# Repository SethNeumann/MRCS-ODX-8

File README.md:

# REPO NAME: MRCS-ODX-8
## License: Creative Commons Attribution-NonCommercial-ShareAlike

High Density Expandable cpOD-M motherboard.  Jon Robinson requested a larger motherboard
comparable to Dr. Chubb's ODMB. The requirement is to get as many cpOD-Ms as possible into a 7
x 15 CM board and provide connectors for expansion. Jon also requested keeping the logic 
level outputs away from the block power outputs.  The board will be expandable via an end
connector.  More than two are not recommended as the copper is only good for about 5 Amps.

ODX-8 are backward compatible with current cpOD-Ms, but mechanically will not fit DCC-ODs.
No software changes are needed.

- Board size 2.7" x 5.8" (69x150 mm)

- DCC Bus connections are 5 mm screw terminal blocks or 0.156 connector for expansion

- power, Ground, and Detector output connections are on a 10-position .100 (2.54 mm) screw terminal block.

The ODX-8 provides an economical and convenient mounting for up to eight cpOD-M detectors 

The ODX-8 mounts in DIN-Rail 70mm snap track or with #4 screws

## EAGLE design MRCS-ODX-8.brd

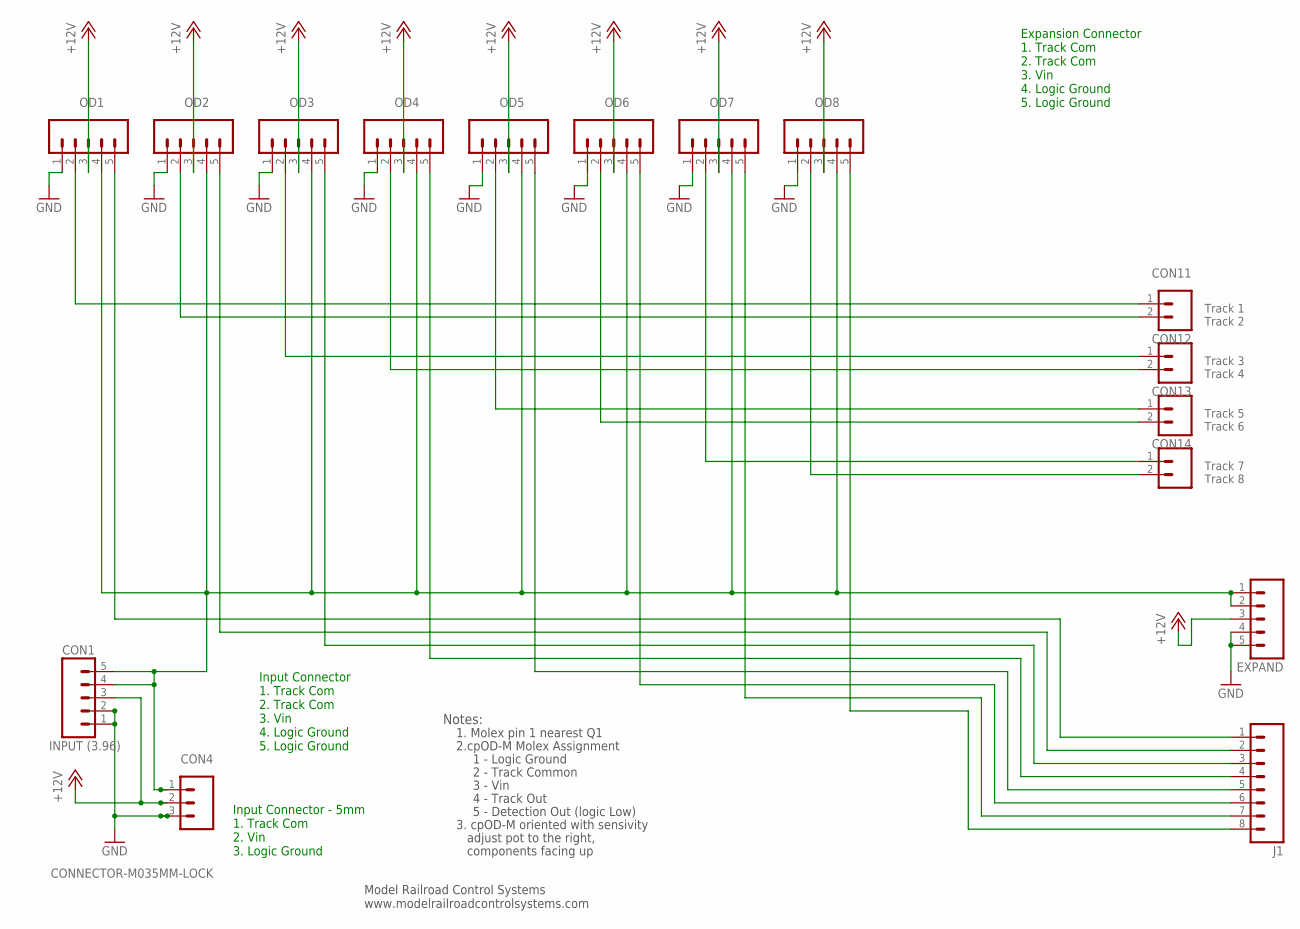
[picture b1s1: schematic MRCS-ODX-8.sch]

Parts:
CON1: INPUT (3.96); KK-156-5
CON4: CONNECTOR-M035MM-LOCK; SCREWTERMINAL-5MM-3
CON11, CON12, CON13, CON14: CONNECTOR-M025MM-LOCK; SCREWTERMINAL-5MM-2
EXPAND: CONNECTOR-M051.56; KK-156-5
J1: CONNECTOR-M08LOCK; 1X08_LOCK
OD1, OD2, OD3, OD4, OD5, OD6, OD7, OD8: CONNECTOR-M051.56; KK-156-5

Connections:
+12V: CON1.3, CON4.2, EXPAND.3, OD1.3, OD2.3, OD3.3, OD4.3, OD5.3, OD6.3, OD7.3, OD8.3
GND: CON1.1, CON1.2, CON4.3, EXPAND.4, EXPAND.5, OD1.1, OD2.1, OD3.1, OD4.1, OD5.1, OD6.1, OD7.1, OD8.1
unnamed: CON14.2 (B), OD8.2
unnamed: CON11.1 (A), OD1.2
unnamed: CON13.2 (B), OD6.2
unnamed: CON13.1 (A), OD5.2
unnamed: J1.2, OD2.5
unnamed: J1.1, OD1.5
unnamed: J1.4, OD4.5
unnamed: J1.5, OD5.5
unnamed: J1.6, OD6.5
unnamed: J1.8, OD8.5
unnamed: J1.7, OD7.5
unnamed: J1.3, OD3.5
unnamed: CON14.1 (A), OD7.2
unnamed: CON12.2 (B), OD4.2
unnamed: CON12.1 (A), OD3.2
unnamed: CON11.2 (B), OD2.2
TRACK_POWER: CON1.4, CON1.5, CON4.1, EXPAND.1, EXPAND.2, OD1.4, OD2.4, OD3.4, OD4.4, OD5.4, OD6.4, OD7.4, OD8.4

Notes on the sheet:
1 - Logic Ground
4 - Track Out
3 - Vin
2 - Track Common
5 - Detection Out (logic Low)
2.cpOD-M Molex Assignment
Notes:
3. cpOD-M oriented with sensivity
adjust pot to the right,
components facing up
Track 1 Track 2
Model Railroad Control Systems www.modelrailroadcontrolsystems.com
1. Molex pin 1 nearest Q1
Input Connector 1. Track Com 2. Track Com 3. Vin 4. Logic Ground 5. Logic Ground
Input Connector - 5mm 1. Track Com 2. Vin 3. Logic Ground
Track 3 Track 4
Track 5 Track 6
Track 7 Track 8
Expansion Connector 1. Track Com 2. Track Com 3. Vin 4. Logic Ground 5. Logic Ground

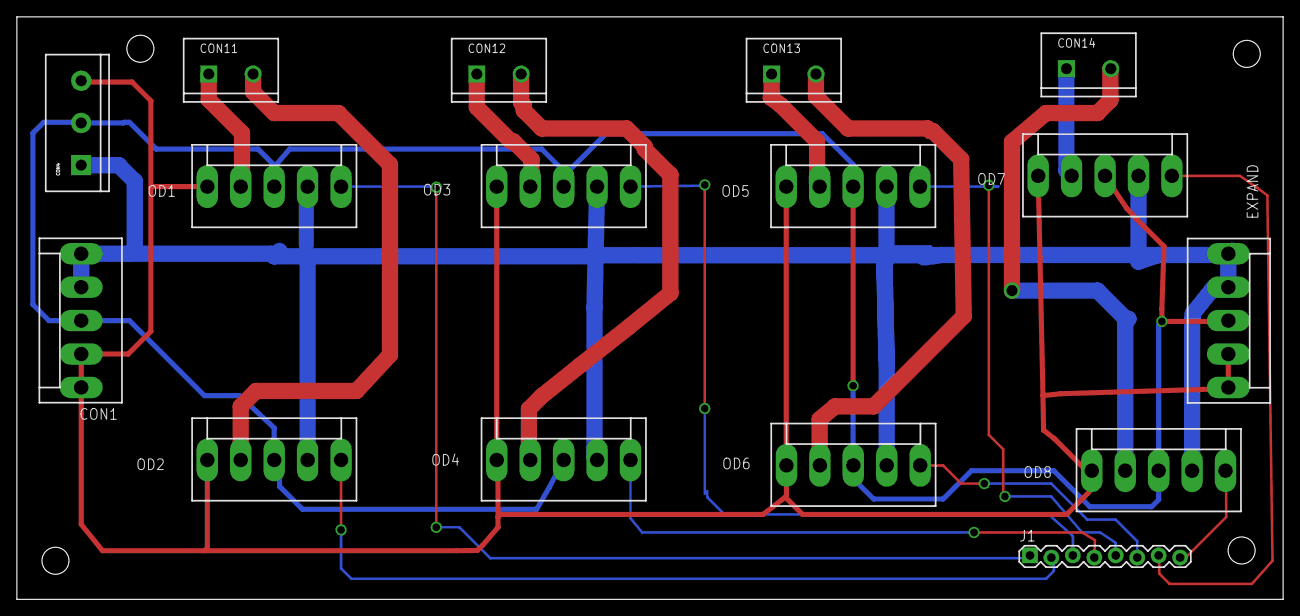
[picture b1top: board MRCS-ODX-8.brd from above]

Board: 2 copper layers, 150.0 x 69.0 mm, 19 parts (0 on the bottom side), 19 nets.

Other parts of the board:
U$1: MRCSLOGOTOP
U$2: MRCSLOGOBTM
U$3: CA-PROP65WARNING

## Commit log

2021-04-04 initial committ
    initial committ
2021-04-04 Update INFO
2021-04-04 intial commit
    initial commit
2021-04-04 Update doc.md
    initial commit
2021-04-04 Update README.md
    initial commit
2021-04-04 copied ODX4 files in to start
    Would have forked but I couldn't figure out how to change the name while forking.
2021-04-15 Release Zero 20210405
    prototypes. Silkscreen on 3 position screw terminal has Track Common and GND reversed, needs adjustment of OD7 and expand needs to be moved inwards. Otherwise electrically OK. Track common bus on bot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
2021-04-15 Revised after prototypes receieved
    cleaned up speculative language as it has been built
2021-04-15 changes after prototypes received
    changed to "fabricated"
2021-04-15 Received prototypes
    minor changes in languages to indicate it has been built and tested.
2021-04-15 prototypes received
    minor changes to indicate the board exists
2021-04-19 Rev 1.1
    corrected Silk Screen error on input connector, moved OD7 connector to make more room. Cleaned up track common bus.
2021-05-05 minor changes and new gerbers
    revised gerbers
